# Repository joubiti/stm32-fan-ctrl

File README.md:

# 12V Fan Controller with STM32 and PID control
## Overview

This project implements a closed-loop fan controller on a custom 4-layer PCB (manufactured at JLCPCB) with an STM32G0 micrcontroller.
The fan speed is controlled using a PWM signal and regulated to a target RPM using a PID controller.
The tachometer output of the fan is measured with a timer input capture unit, filtered, and fed into the control loop.
Fairly satisfactory control performances have been achieved with Kp=0.01, Ki=0.015, and Kd = 0.001 at 10Hz.

## Hardware features

4 layer board designed with KiCAD, and manufactured at JLCPCB for roughly 100 euros total (including shipping) for 2PCBA and 3PCBs, very minimal and cheap BOM. Production files are in Hardware/Production.

* **Buck Converter** takes 12V input from DC input jack and generates 5V rail (for PWM)
* **Linear Regulator** generates 3.3V rail from 5V (for MCU signals)
* **N-channel MOSFET** for low-side switching to generate appropriate PWM signals for 4-wire fan, inverting logic in firmware
* **Tachometer** open collector input for fan RPM measurement (hardware timer)

Schematics are given below:

PCB layout:

3D view:

Manufactured & assembled boards:

## System Architecture

* **Tachometer**: Measures period between tach pulses, converts to RPM (tachometer.h, tachometer.c)
* **First order IIR low pass filter**: Smooths RPM measurement (low_pass_filter.h, low_pass_filter.c)
* **PID controller**: Computes duty cycle command from target vs. measured RPM (pid_controller.h, pid_controller.c)
* **Fan speed controller**: Applies PWM duty cycle to MOSFET (fan_speed_controller.h, fan_speed_controller.c)
* **Application loop**: Handles control functions at 10 Hz, heartbeat at 1Hz, logging at 0.5Hz

```
  while (1)
  {
    /**************************** CONTROL LOOP (10 Hz) ****************** */
    tachometer_update_rpm(&fan_tachometer, HAL_GetTick());
    low_pass_filter_update(&rpm_filter, fan_tachometer.current_rpm, HAL_GetTick());
    uint8_t command = pid_controller_step(&pid, (uint32_t)rpm_filter.last_sample, RPM_SETPOINT, HAL_GetTick());
    if(command != PID_NO_UPDATE)
    {
      fan_set_rpm_percent(&fan_controller, command);
    }
    /******************************************************************** */

    /************************** HEARTBEAT LED & PERIODIC UART MESSAGES ****** */
    heartbeat_toggle(&heartbeat_led, HAL_GetTick());
    logging_send_periodic_msg(HAL_GetTick(), "Fan RPM: %d \n", fan_tachometer.current_rpm);
    /************************************************************************ */
  }
```

## System performances

After tuning PID controller and testing various setpoints, we have reached the following system response.

For 5000 RPM:

For 8000 RPM:

It's possible to achieve better performances, but for the sake of this project and for my use-case, this is satisfying enough.
The plots were generated with MCUViewer, which enables live capture of global variables with static addresses through SWD/JTAG.

## Building

To build the code, it is enough to run "make" in the "Software" directory. Assuming arm-none-eabi-gcc is correctly installed and configured for $PATH.
KiCAD Files are provided in Hardware/, and JLCPCB production files in Hardware/Production.

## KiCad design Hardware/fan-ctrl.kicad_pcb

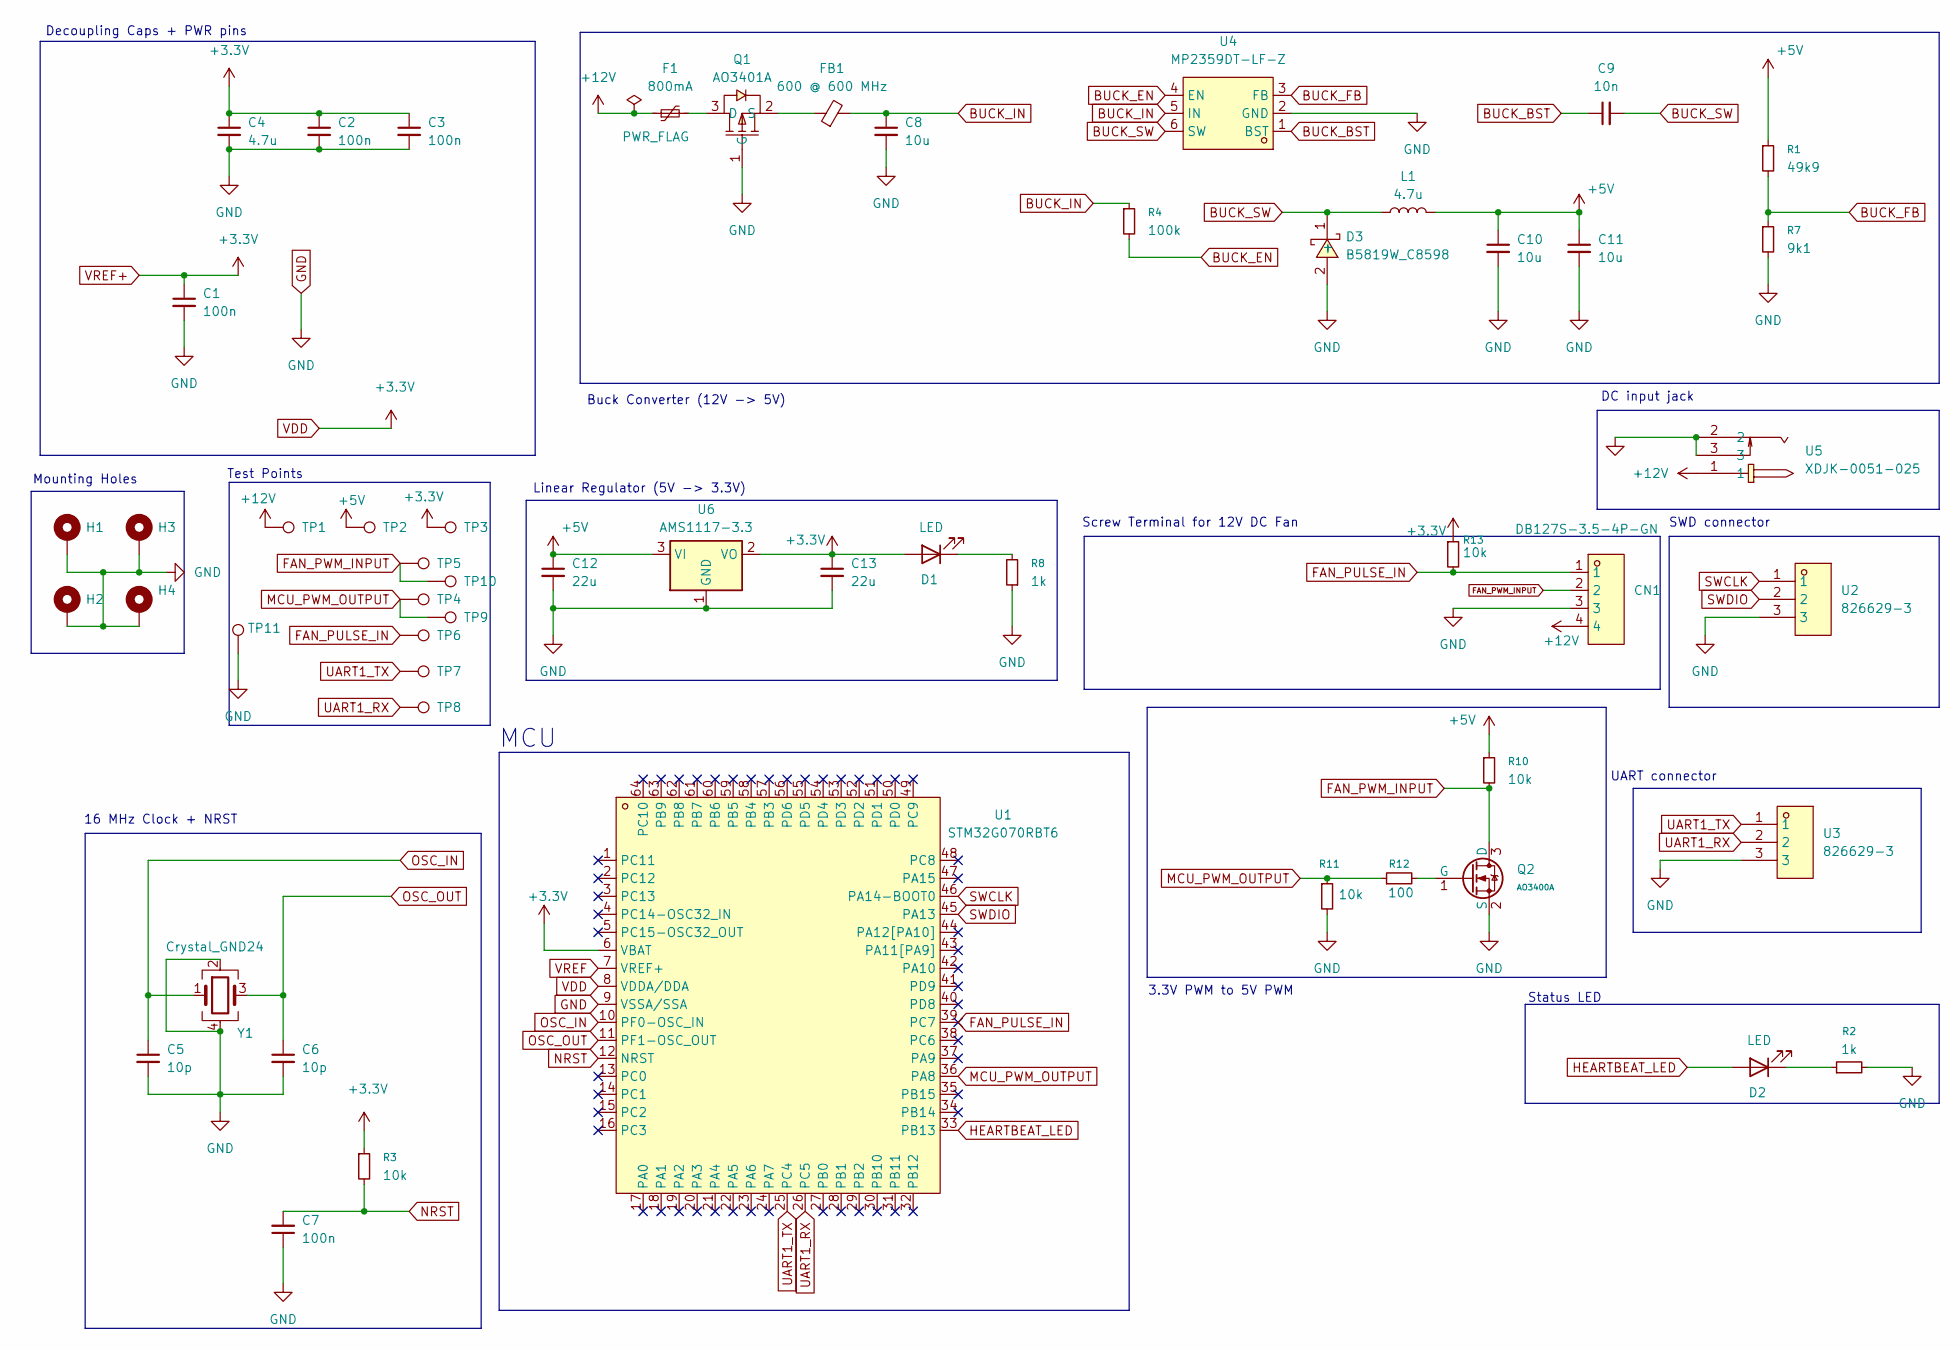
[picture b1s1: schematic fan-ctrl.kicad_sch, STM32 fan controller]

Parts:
C1, C2, C3, C7: 100n; C_0402_1005Metric
C4: 4.7u; C_0402_1005Metric
C5, C6: 10p; C_0402_1005Metric
C8, C10, C11: 10u; C_1206_3216Metric
C9: 10n; C_1206_3216Metric
C12, C13: 22u; C_1206_3216Metric
CN1: DB127S-3.5-4P-GN; CONN-TH_4P-P3.50_DIBO_DB127S-3.5-4P-GN; LCSC Part C2997511
D1: LED; LED_0805_2012Metric
D2: LED; LED_0402_1005Metric
D3: B5819W_C8598; SOD-123_L2.7-W1.6-LS3.7-RD-1; LCSC Part C8598
F1: 800mA; Fuse_1206_3216Metric
FB1: 600 @ 600 MHz; L_1206_3216Metric
H1, H2, H3, H4: MountingHole_Pad; MountingHole_2.2mm_M2_Pad_Via
L1: 4.7u; L_1206_3216Metric
Q1: AO3401A; SOT-23_L2.9-W1.3-P1.90-LS2.4-BR; LCSC Part C15127
Q2: AO3400A; Q_SOT-23; Part AO3400A; LCSC C20917
R1: 49k9; R_0603
R2, R8: 1k; R_0402
R3, R11: 10k; R_0402
R4: 100k; R_0603
R7: 9k1; R_0603
R10, R13: 10k; R_0603
R12: 100; R_0402
TP1, TP2, TP3, TP5, TP6: TestPoint; TestPoint_Pad_D3.0mm
TP4, TP7, TP8: TestPoint; TestPoint_Pad_D2.0mm
TP9, TP10, TP11: TestPoint; TestPoint_THTPad_D1.0mm_Drill0.5mm
U1: STM32G070RBT6; LQFP-64_L10.0-W10.0-P0.50-LS12.0-BL; LCSC Part C529340
U2, U3: 826629-3; HDR-TH_3P-P2.54-V-M-1; LCSC Part C306127
U4: MP2359DT-LF-Z; SOT-23-6_L2.9-W1.6-P0.95-LS2.8-BR; LCSC Part C6595509
U5: XDJK-0051-025; DC-IN-TH_XDJK-0051-025; LCSC Part C7498153
U6: AMS1117-3.3; SOT-223-3_TabPin2
Y1: Crystal_GND24; Crystal_SMD_3225-4Pin_3.2x2.5mm

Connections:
+5V: C10.1, C11.1, C12.1, L1.2, R1.1, R10.1, TP2.1, U6.3 (VI)
+12V: CN1.4, F1.1, TP1.1, U5.1
BUCK_BST: C9.1, U4.1 (BST)
BUCK_EN: R4.2, U4.4 (EN)
BUCK_FB: R1.2, R7.1, U4.3 (FB)
BUCK_IN: C8.1, FB1.2, R4.1, U4.5 (IN)
BUCK_SW: C9.2, D3.1 (-), L1.1, U4.6 (SW)
FAN_PULSE_IN: CN1.1, R13.2, TP6.1, U1.39 (PC7); also elsewhere on the board
FAN_PWM_INPUT: CN1.2, Q2.3 (D), R10.2, TP5.1, TP10.1
GND: C1.2, C2.2, C3.2, C4.2, C5.2, C6.2, C7.1, C8.2, C10.2, C11.2, C12.2, C13.2, CN1.3, D3.2 (+), H1.1, H2.1, H3.1, H4.1, Q1.1 (G), Q2.2 (S), R2.2, R7.2, R8.1, R11.2, TP11.1, U1.9 (VSSA/SSA), U2.3, U3.3, U4.2 (GND), U5.2, U5.3, U6.1 (GND), Y1.2, Y1.4
HEARTBEAT_LED: D2.2 (A), U1.33 (PB13)
MCU_PWM_OUTPUT: R11.1, R12.1, TP4.1, TP9.1, U1.36 (PA8)
NRST: C7.2, R3.2, U1.12 (NRST)
unnamed: D1.1 (K), R8.2
unnamed: D2.1 (K), R2.1
unnamed: F1.2, Q1.3 (D)
unnamed: FB1.1, Q1.2 (S)
unnamed: Q2.1 (G), R12.2
OSC_IN: C5.1, U1.10 (PF0-OSC_IN), Y1.1
OSC_OUT: C6.1, U1.11 (PF1-OSC_OUT), Y1.3
SWCLK: U1.46 (PA14-BOOT0), U2.1
SWDIO: U1.45 (PA13), U2.2
UART1_RX: TP8.1, U1.26 (PC5), U3.2
UART1_TX: TP7.1, U1.25 (PC4), U3.1
VDD: C1.1, C2.1, C3.1, C4.1, C13.1, D1.2 (A), R3.1, R13.1, TP3.1, U1.6 (VBAT), U1.8 (VDDA/DDA), U6.2 (VO); also elsewhere on the board
VREF: U1.7 (VREF+)

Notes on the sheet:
MCU
UART connector
Buck Converter (12V -> 5V)
Linear Regulator (5V -> 3.3V)
Status LED
Screw Terminal for 12V DC Fan
Test Points
16 MHz Clock + NRST
SWD connector
DC input jack
Decoupling Caps + PWR pins
3.3V PWM to 5V PWM
Mounting Holes

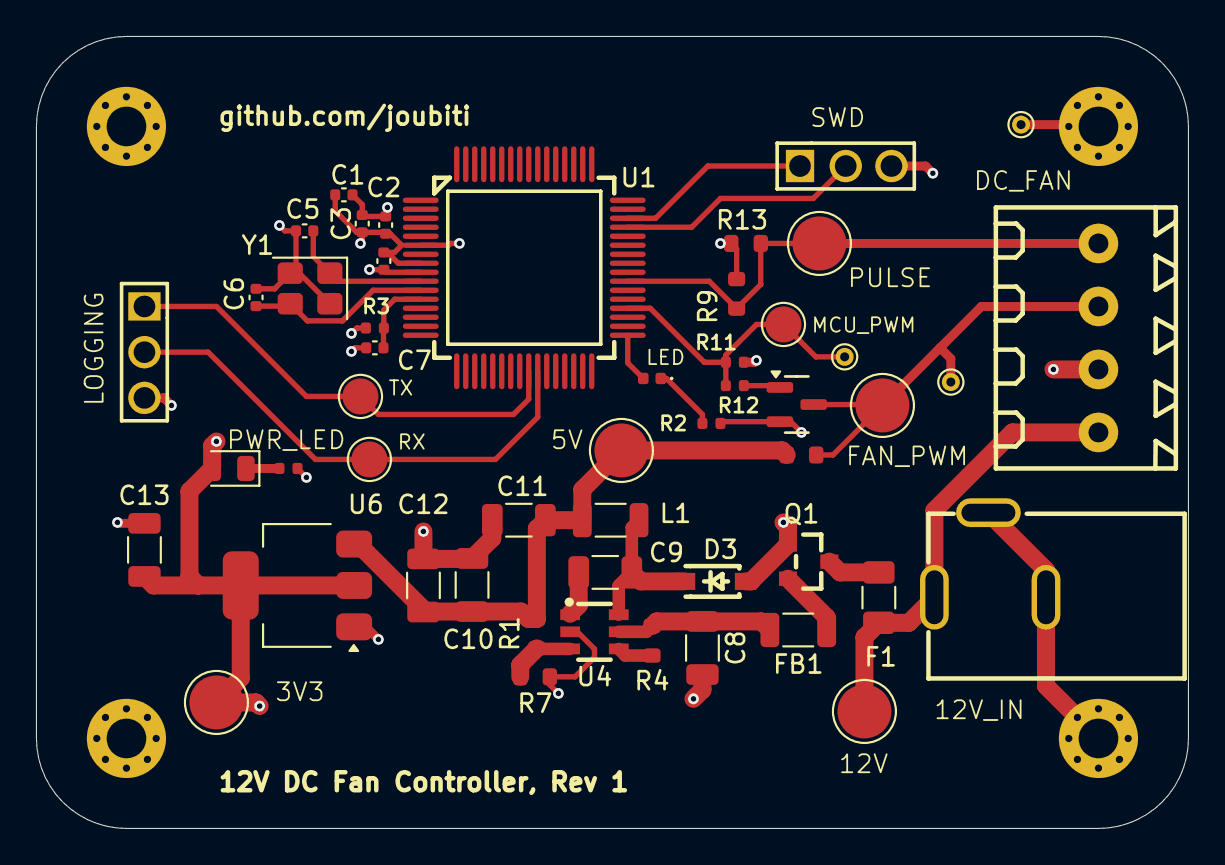
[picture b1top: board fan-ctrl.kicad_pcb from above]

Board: 4 copper layers, 64.0 x 44.0 mm, 55 parts (0 on the bottom side), 25 nets.

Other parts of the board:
R9: 10k; R_0603

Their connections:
FAN_PULSE_IN: R9.2; also elsewhere on the board
VDD: R9.1; also elsewhere on the board

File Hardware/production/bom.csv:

Designator,Footprint,Quantity,Value,LCSC Part #
"C1, C2, C3, C7",0402,4,100n,
"C10, C11, C12, C13, C8",1206,5,10u,
C4,0402,1,4.7u,
"C5, C6",0402,2,10p,
C9,1206,1,10n,
CN1,CONN-TH_4P-P3.50_DIBO_DB127S-3.5-4P-GN,1,DB127S-3.5-4P-GN,C2997511
D1,0805,1,LED,
D2,0402,1,LED,
D3,SOD-123_L2.7-W1.6-LS3.7-RD-1,1,B5819W_C8598,C8598
F1,1206,1,500mA,
FB1,1206,1,600 @ 600 MHz,
L1,1206,1,4.7u,
Q1,SOT-23_L2.9-W1.3-P1.90-LS2.4-BR,1,AO3401A,C15127
Q2,Q_SOT-23,1,AO3400A,C20917
R1,R_0603,1,49k9,
"R10, R13, R9",R_0603,3,10k,
"R11, R3",R_0402,2,10k,
R12,R_0402,1,100,
"R2, R8",R_0402,2,1k,
R4,R_0603,1,100k,
R7,R_0603,1,9k1,
"TP1, TP2, TP3, TP5, TP6",TestPoint_Pad_D3.0mm,5,TestPoint,
"TP10, TP11, TP9",TestPoint_THTPad_D1.0mm_Drill0.5mm,3,TestPoint,
"TP4, TP7, TP8",TestPoint_Pad_D2.0mm,3,TestPoint,
U1,LQFP-64_L10.0-W10.0-P0.50-LS12.0-BL,1,STM32G070RBT6,C529340
"U2, U3",HDR-TH_3P-P2.54-V-M-1,2,826629-3,C306127
U4,SOT-23-6_L2.9-W1.6-P0.95-LS2.8-BR,1,MP2359DT-LF-Z,C6595509
U5,DC-IN-TH_XDJK-0051-025,1,XDJK-0051-025,C7498153
U6,SOT-223-3_TabPin2,1,AMS1117-3.3,
Y1,Crystal_SMD_3225-4Pin_3.2x2.5mm,1,Crystal_GND24,

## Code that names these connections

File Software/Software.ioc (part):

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Mcu.Name=STM32G070RBTx
Mcu.Package=LQFP64
Mcu.UserName=STM32G070RBTx
PA13.Mode=Serial_Wire
PA13.Signal=SYS_SWDIO
PA14-BOOT0.Mode=Serial_Wire
PA14-BOOT0.Signal=SYS_SWCLK
PA8.Signal=S_TIM1_CH1
PB13.Signal=GPIO_Output
PC4.Mode=Asynchronous
PC4.Signal=USART1_TX
PC5.Mode=Asynchronous
PC5.Signal=USART1_RX
PC7.Signal=S_TIM3_CH2
PF0-OSC_IN\ (PF0).Mode=HSE-External-Oscillator
PF0-OSC_IN\ (PF0).Signal=RCC_OSC_IN
PF1-OSC_OUT\ (PF1).Mode=HSE-External-Oscillator
PF1-OSC_OUT\ (PF1).Signal=RCC_OSC_OUT
RCC.HSE_VALUE=16000000
RCC.SYSCLKFreq_VALUE=64000000
RCC.SYSCLKSource=RCC_SYSCLKSOURCE_PLLCLK
board=custom

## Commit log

2025-08-30 Initial layout (MCU, crystal circuitry, buck converter)
2025-08-31 Update buck converter circuit (5V output), add switching linear regulator for 3.3V output, add N-channel MOSFET for 5V PWM control
2025-08-31 Add mounting holes, test points, initial footprint assignment, next up:review design and buck converter output, review available footprints in JLCPCB
2025-08-31 Component placement, board edge cuts, adjust some footprints, testpoints, silkscreen for connectors and testpoints, next: review footprints JLCPCB before routing
2025-08-31 Adjust board dimensions and edge cuts
2025-09-01 Update buck converter circuit, standard R values for close 5V output, double-checked footprints available in JLCPCB
2025-09-02 Update schematics (polyfuse value, capacitor values in linear regulatorcircuit, use different HW timer enabled pin for the fan pulse input
2025-09-06 Add board schematics to readme
2025-09-06 Add 3D of board
2025-09-08 Received PCBs from JLC, board bring-up: heartbeat LED OK, next up: UARTinterface
2025-09-08 Push logging module, UART working on board, next up: 50% square wave on PWM
2025-09-09 Board bring-up: defining timer for input capture and frequency measurement. 0% duty cycle means fan running at very low speeds, 100% is max speed
2025-09-12 First prototype of tachometer module, seems to be roughly OK (timer sampling at 1 MHz), to do: handle overflows and moving average filter
2025-09-13 Add fan speed controller module, for 0-100% speed modulation based on PWM
2025-09-14 Implement and tune PID controller, implement first order IIR low pass filter for tachometer reading, minor adjustments in main loop
